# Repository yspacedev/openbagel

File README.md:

# openbagel
An open source, simple to assemble plasma toroid driver (specifically for Zerg Labs 1L flasks)

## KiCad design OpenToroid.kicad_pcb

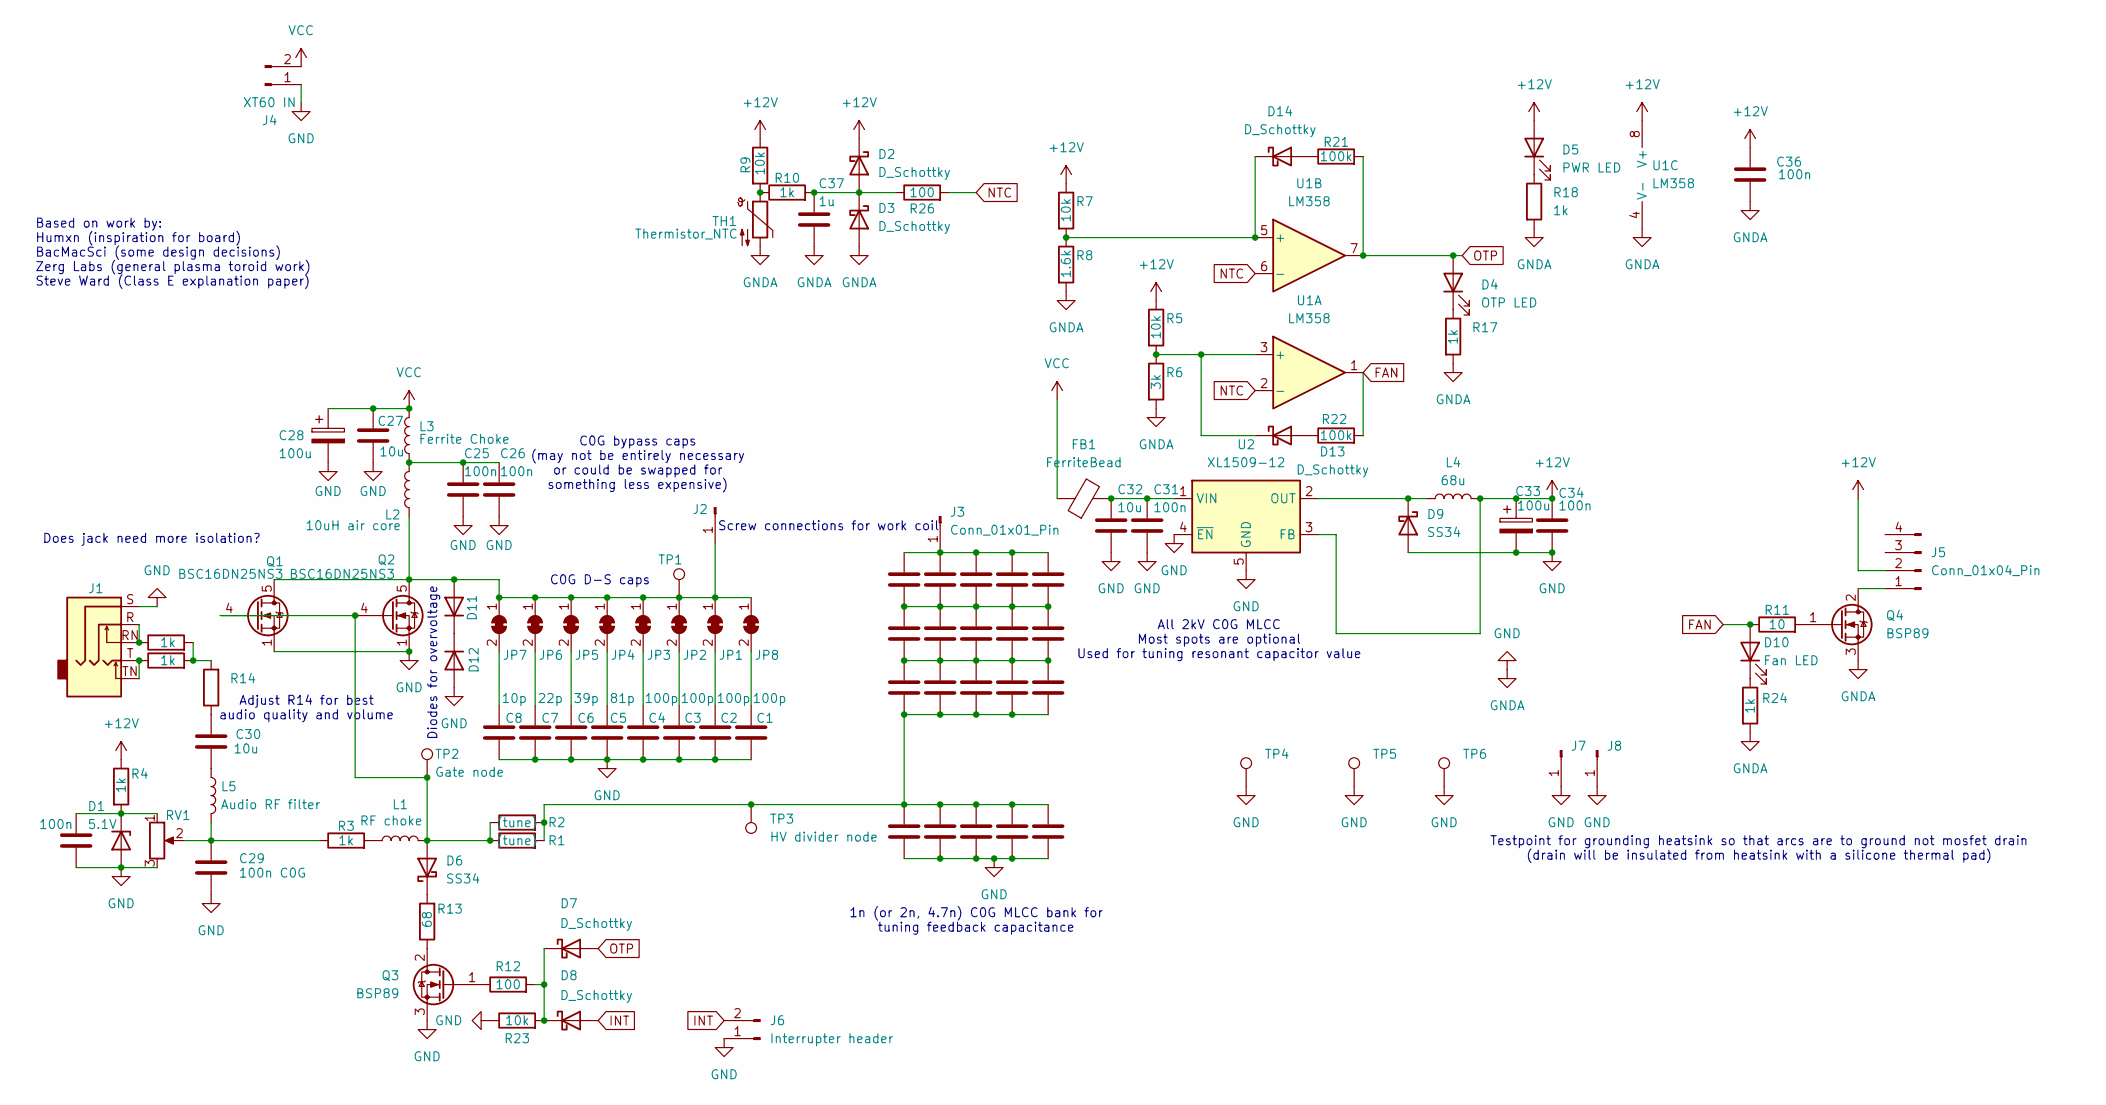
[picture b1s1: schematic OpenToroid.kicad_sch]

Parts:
C1, C2, C3, C4: 100p; C_1206_3216Metric
C5: 81p; C_1206_3216Metric
C6: 39p; C_1206_3216Metric
C7: 22p; C_1206_3216Metric
C8: 10p; C_1206_3216Metric
C9, C10, C11, C12, C13, C14, C15, C16, C17, C18, C19, C20, C21, C22, C23, C24, C38, C39, C40, C41: C; C_1206_3216Metric
C25, C26: 100n; C_1812_4532Metric
C27, C30, C32: 10u; C_1206_3216Metric
C28: 100u; CP_Elec_8x10
C29: 100n C0G; C_1206_3216Metric
C31, C34, C35, C36: 100n; C_0805_2012Metric
C33: 100u; CP_Elec_6.3x7.7
C37: 1u; C_0805_2012Metric
D1: 5.1V; D_SOD-123
D2, D3, D7, D8, D13, D14: D_Schottky; D_SOD-123
D4: OTP LED; LED_0805_2012Metric
D5: PWR LED; LED_0805_2012Metric
D6, D9: SS34; D_SMA
D10: Fan LED; LED_0805_2012Metric
D11, D12: D; D_SMA
FB1: FerriteBead; L_0805_2012Metric
J1: AudioJack3_SwitchTR; Jack_3.5mm_Ledino_KB3SPRS_Horizontal
J2, J3: Conn_01x01_Pin; M4 Plugin PCB Mount Screw Terminal
J4: XT60 IN; AMASS_XT60PW-F_1x02_P7.20mm_Horizontal
J5: Conn_01x04_Pin; PinSocket_1x04_P2.54mm_Vertical
J6: Interrupter header; PinHeader_1x02_P2.54mm_Vertical
J7, J8: Conn_01x01_Pin; OpenBagel Padded Screw
JP1, JP2, JP3, JP4, JP5, JP6, JP7, JP8: SolderJumper_2_Bridged; SolderJumper-2_P1.3mm_Bridged_RoundedPad1.0x1.5mm
L1: RF choke; L_Toroid_Vertical_L10.0mm_W5.0mm_P5.08mm
L2: 10uH air core; OpenBagel feed inductor
L3: Ferrite Choke; LairdTech_28C0236-0JW-10
L4: 68u; L_Sunlord_SWPA6045S
L5: Audio RF filter; L_Toroid_Vertical_L10.0mm_W5.0mm_P5.08mm
Q1, Q2: BSC16DN25NS3; TDSON-8-1
Q3, Q4: BSP89; SOT-223-3_TabPin2
R1, R2: (tune); R_2512_6332Metric
R3, R4: 1k; R_1206_3216Metric
R5, R7, R9, R23: 10k; R_0805_2012Metric
R6: 3k; R_0805_2012Metric
R8: 1.6k; R_0805_2012Metric
R10, R15, R16, R17, R18, R24: 1k; R_0805_2012Metric
R11: 10; R_0805_2012Metric
R12, R26: 100; R_0805_2012Metric
R13: 68; R_1206_3216Metric
R14: adjust for best audio \n volume and quality; R_0805_2012Metric
R21, R22: 100k; R_0805_2012Metric
RV1: R_Potentiometer; Potentiometer_Alps_RK09K_Single_Horizontal
TH1: Thermistor_NTC; R_0805_2012Metric
TP1, TP4, TP5, TP6: TestPoint; TestPoint_Pad_2.0x2.0mm
TP2: Gate node; TestPoint_Pad_2.0x2.0mm
TP3: HV divider node; TestPoint_Pad_2.0x2.0mm
U1: LM358; SOIC-8_3.9x4.9mm_P1.27mm
U2: XL1509-12; SOIC-8_3.9x4.9mm_P1.27mm

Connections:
+12V: C33.1, C34.1, C36.1, D2.1 (K), D5.2 (A), J5.2, L4.2, R4.1, R5.1, R7.1, R9.1, U1.8 (V+), U2.3 (FB)
FAN: D10.2 (A), R11.1, R22.2, U1.1
GND: C1.1, C2.1, C3.1, C4.1, C5.2, C6.2, C7.2, C8.2, C9.2, C10.2, C11.2, C12.2, C25.2, C26.2, C27.2, C28.2, C29.2, C31.2, C32.2, C33.2, C34.2, C35.2, C36.2, C37.2, C41.2, D1.2 (A), D3.2 (A), D9.2 (A), D12.2 (A), J1.S, J4.1, J6.1, J7.1, J8.1, Q1.1 (S), Q1.2 (S), Q1.3 (S), Q2.1 (S), Q2.2 (S), Q2.3 (S), Q3.3 (S), Q4.3 (S), R6.2, R8.2, R17.2, R18.2, R23.1, R24.2, RV1.3, TH1.2, TP4.1, TP5.1, TP6.1, U1.4 (V-), U2.4 (~EN), U2.5 (GND), U2.6 (GND), U2.7 (GND), U2.8 (GND)
INT: D8.2 (A), J6.2
NTC: R26.2, U1.2 (-), U1.6 (-)
unnamed: C9.1, C10.1, C11.1, C12.1, C13.2, C14.2, C15.2, C16.2, C40.2, C41.1, R1.2, R2.2, TP3.1
unnamed: C13.1, C14.1, C15.1, C16.1, C17.2, C18.2, C19.2, C20.2, C39.2, C40.1
unnamed: C17.1, C18.1, C19.1, C20.1, C21.2, C22.2, C23.2, C24.2, C38.2, C39.1
unnamed: C25.1, C26.1, L2.2, L3.1
unnamed: C29.1, L5.2, R3.1, RV1.2
unnamed: C30.1, R14.1
unnamed: C30.2, L5.1
unnamed: C35.1, D1.1 (K), R4.2, RV1.1
unnamed: C37.1, D2.2 (A), D3.1 (K), R10.2, R26.1
unnamed: D4.1 (K), R17.1
unnamed: D5.1 (K), R18.1
unnamed: D6.2 (A), L1.2, Q1.4 (G), Q2.4 (G), R1.1, R2.1, TP2.1
unnamed: D6.1 (K), R13.2
unnamed: D7.1 (K), D8.1 (K), R12.2, R23.2
unnamed: D9.1 (K), L4.1, U2.2 (OUT)
unnamed: D10.1 (K), R24.1
unnamed: D11.2 (A), J2.1, JP1.1 (A), JP2.1 (A), JP3.1 (A), JP4.1 (A), JP5.1 (A), JP6.1 (A), JP7.1 (A), JP8.1 (A), L2.1, Q1.5 (D), Q2.5 (D), TP1.1
unnamed: D11.1 (K), D12.1 (K)
unnamed: D13.2 (A), R22.1
unnamed: D13.1 (K), R5.2, R6.1, U1.3 (+)
unnamed: D14.2 (A), R21.1
unnamed: D14.1 (K), R7.2, R8.1, U1.5 (+)
unnamed: J1.R, J1.RN, R15.1
unnamed: J1.T, J1.TN, R16.1
unnamed: C21.1, C22.1, C23.1, C24.1, C38.1, J3.1
unnamed: J5.1, Q4.2 (D)
unnamed: C2.2, JP1.2 (B)
unnamed: C3.2, JP2.2 (B)
unnamed: C4.2, JP3.2 (B)
unnamed: C5.1, JP4.2 (B)
unnamed: C6.1, JP5.2 (B)
unnamed: C7.1, JP6.2 (B)
unnamed: C8.1, JP7.2 (B)
unnamed: C1.2, JP8.2 (B)
unnamed: L1.1, R3.2
unnamed: Q3.2 (D), R13.1
unnamed: Q3.1 (G), R12.1
unnamed: Q4.1 (G), R11.2
unnamed: R9.2, R10.1, TH1.1
unnamed: R14.2, R15.2, R16.2
unnamed: C31.1, C32.1, FB1.2, U2.1 (VIN)
OTP: D4.2 (A), D7.2 (A), R21.2, U1.7
VCC: C27.1, C28.1, FB1.1, J4.2, L3.2

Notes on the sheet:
C0G D-S caps
All 2kV C0G MLCC Most spots are optional Used for tuning resonant capacitor value
Testpoint for grounding heatsink so that arcs are to ground not mosfet drain (drain will be insulated from heatsink with a silicone thermal pad)
Does jack need more isolation?
Screw connections for work coil
Based on work by: Humxn (inspiration for board) BacMacSci (some design decisions) Zerg Labs (general plasma toroid work) Steve Ward (Class E explanation paper)
Diodes for overvoltage
C0G bypass caps (may not be entirely necessary or could be swapped for something less expensive)
1n (or 2n, 4.7n) C0G MLCC bank for tuning feedback capacitance
Adjust R14 for best audio quality and volume

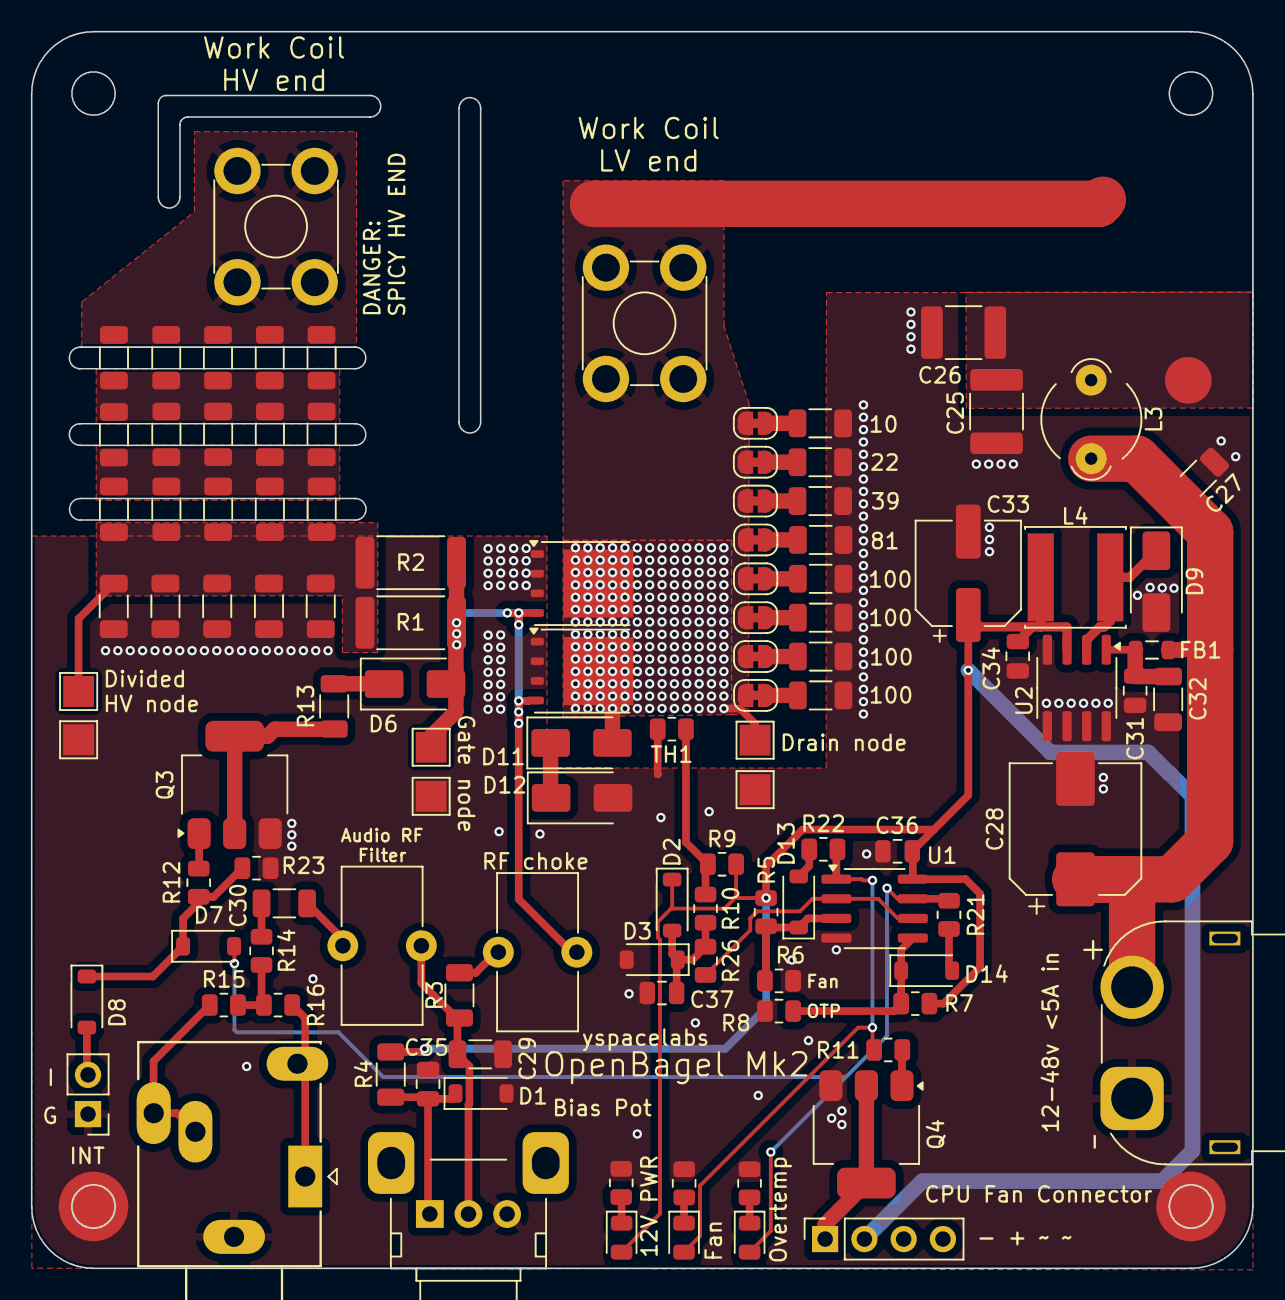
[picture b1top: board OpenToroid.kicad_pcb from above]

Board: 2 copper layers, 79.0 x 80.0 mm, 113 parts (0 on the bottom side), 48 nets.

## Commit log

2024-10-20 Initial commit
    Note: files are not complete. I'm working on a V2 revision that fixes some problems and these files are a WIP
